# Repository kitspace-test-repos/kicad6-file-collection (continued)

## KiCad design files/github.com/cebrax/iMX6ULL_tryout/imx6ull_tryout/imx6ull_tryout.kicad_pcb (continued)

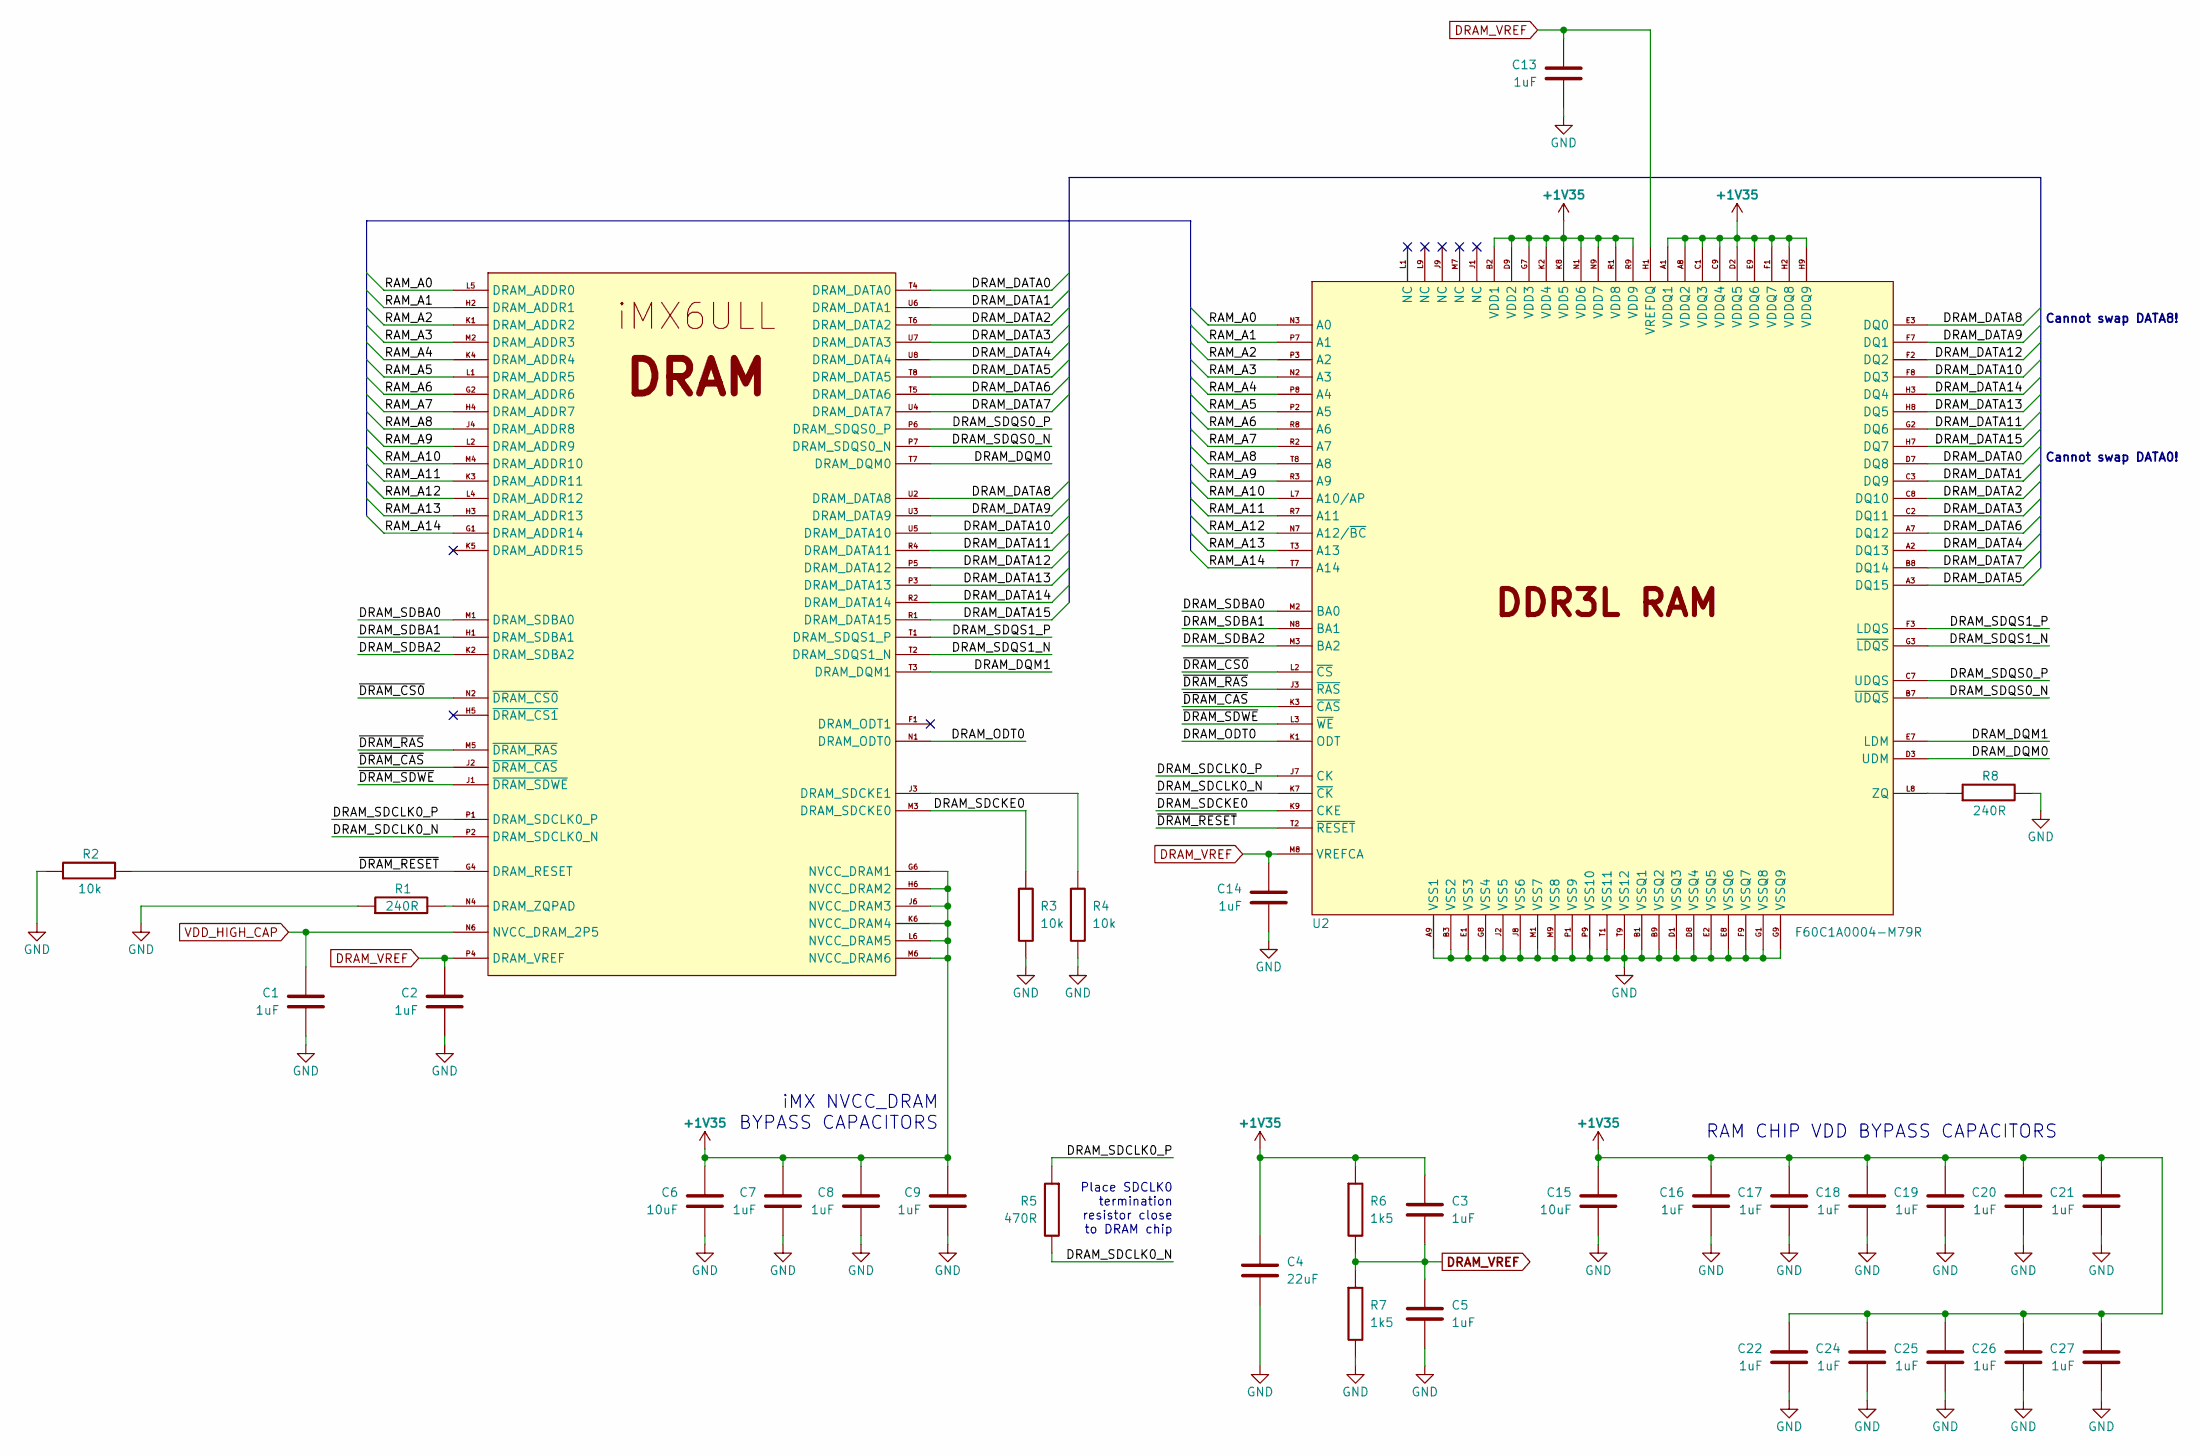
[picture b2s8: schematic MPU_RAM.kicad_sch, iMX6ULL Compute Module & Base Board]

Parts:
C1, C2, C7, C8, C9, C13, C14, C16, C17, C18, C19, C20, C21, C22, C24, C25, C26, C27: 1uF; IPC-SMD-C-0402; Voltage 10V
C3, C5: 1uF; IPC-SMD-C-0603; Voltage 16V
C4: 22uF; IPC-SMD-C-0603; Voltage 6.3V
C6: 10uF; IPC-SMD-C-0402; Voltage 16V
C15: 10uF; IPC-SMD-C-0805; Voltage 16V
R1, R8: 240R; IPC-SMD-R-0402
R2, R3, R4: 10k; IPC-SMD-R-0402
R5: 470R; IPC-SMD-R-0402
R6, R7: 1k5; IPC-SMD-R-0603
U1: iMX6ULL; BGA289C80P17X17_1400X1400X132N
U2: F60C1A0004-M79R; BGA96C80P9X16_1400X800X120

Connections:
+1V35: C3.1, C4.1, C6.1, C7.1, C8.1, C9.1, C15.1, C16.1, C17.1, C18.1, C19.1, C20.1, C21.1, C22.1, C24.1, C25.1, C26.1, C27.1, R6.1, U1.G6 (NVCC_DRAM1), U1.H6 (NVCC_DRAM2), U1.J6 (NVCC_DRAM3), U1.K6 (NVCC_DRAM4), U1.L6 (NVCC_DRAM5), U1.M6 (NVCC_DRAM6), U2.A1 (VDDQ1), U2.A8 (VDDQ2), U2.B2 (VDD1), U2.C1 (VDDQ3), U2.C9 (VDDQ4), U2.D2 (VDDQ5), U2.D9 (VDD2), U2.E9 (VDDQ6), U2.F1 (VDDQ7), U2.G7 (VDD3), U2.H2 (VDDQ8), U2.H9 (VDDQ9), U2.K2 (VDD4), U2.K8 (VDD5), U2.N1 (VDD6), U2.N9 (VDD7), U2.R1 (VDD8), U2.R9 (VDD9); also elsewhere on the board
/MPU_DRAM/DRAM_DATA0: U1.T4 (DRAM_DATA0), U2.D7 (DQ8)
/MPU_DRAM/DRAM_DATA1: U1.U6 (DRAM_DATA1), U2.C3 (DQ9)
/MPU_DRAM/DRAM_DATA2: U1.T6 (DRAM_DATA2), U2.C8 (DQ10)
/MPU_DRAM/DRAM_DATA3: U1.U7 (DRAM_DATA3), U2.C2 (DQ11)
/MPU_DRAM/DRAM_DATA4: U1.U8 (DRAM_DATA4), U2.A2 (DQ13)
/MPU_DRAM/DRAM_DATA5: U1.T8 (DRAM_DATA5), U2.A3 (DQ15)
/MPU_DRAM/DRAM_DATA6: U1.T5 (DRAM_DATA6), U2.A7 (DQ12)
/MPU_DRAM/DRAM_DATA7: U1.U4 (DRAM_DATA7), U2.B8 (DQ14)
/MPU_DRAM/DRAM_DATA8: U1.U2 (DRAM_DATA8), U2.E3 (DQ0)
/MPU_DRAM/DRAM_DATA9: U1.U3 (DRAM_DATA9), U2.F7 (DQ1)
/MPU_DRAM/DRAM_DATA10: U1.U5 (DRAM_DATA10), U2.F8 (DQ3)
/MPU_DRAM/DRAM_DATA11: U1.R4 (DRAM_DATA11), U2.G2 (DQ6)
/MPU_DRAM/DRAM_DATA12: U1.P5 (DRAM_DATA12), U2.F2 (DQ2)
/MPU_DRAM/DRAM_DATA13: U1.P3 (DRAM_DATA13), U2.H8 (DQ5)
/MPU_DRAM/DRAM_DATA14: U1.R2 (DRAM_DATA14), U2.H3 (DQ4)
/MPU_DRAM/DRAM_DATA15: U1.R1 (DRAM_DATA15), U2.H7 (DQ7)
/MPU_DRAM/DRAM_DQM0: U1.T7 (DRAM_DQM0), U2.D3 (UDM)
/MPU_DRAM/DRAM_DQM1: U1.T3 (DRAM_DQM1), U2.E7 (LDM)
/MPU_DRAM/DRAM_ODT0: U1.N1 (DRAM_ODT0), U2.K1 (ODT)
/MPU_DRAM/DRAM_SDBA0: U1.M1 (DRAM_SDBA0), U2.M2 (BA0)
/MPU_DRAM/DRAM_SDBA1: U1.H1 (DRAM_SDBA1), U2.N8 (BA1)
/MPU_DRAM/DRAM_SDBA2: U1.K2 (DRAM_SDBA2), U2.M3 (BA2)
/MPU_DRAM/DRAM_SDCKE0: R3.1, U1.M3 (DRAM_SDCKE0), U2.K9 (CKE)
/MPU_DRAM/DRAM_SDCLK0_N: R5.2, U1.P2 (DRAM_SDCLK0_N), U2.K7 (~CK~)
/MPU_DRAM/DRAM_SDCLK0_P: R5.1, U1.P1 (DRAM_SDCLK0_P), U2.J7 (CK)
/MPU_DRAM/DRAM_SDQS0_N: U1.P7 (DRAM_SDQS0_N), U2.B7 (~UDQS~)
/MPU_DRAM/DRAM_SDQS0_P: U1.P6 (DRAM_SDQS0_P), U2.C7 (UDQS)
/MPU_DRAM/DRAM_SDQS1_N: U1.T2 (DRAM_SDQS1_N), U2.G3 (~LDQS~)
/MPU_DRAM/DRAM_SDQS1_P: U1.T1 (DRAM_SDQS1_P), U2.F3 (LDQS)
/MPU_DRAM/RAM_A0: U1.L5 (DRAM_ADDR0), U2.N3 (A0)
/MPU_DRAM/RAM_A1: U1.H2 (DRAM_ADDR1), U2.P7 (A1)
/MPU_DRAM/RAM_A2: U1.K1 (DRAM_ADDR2), U2.P3 (A2)
/MPU_DRAM/RAM_A3: U1.M2 (DRAM_ADDR3), U2.N2 (A3)
/MPU_DRAM/RAM_A4: U1.K4 (DRAM_ADDR4), U2.P8 (A4)
/MPU_DRAM/RAM_A5: U1.L1 (DRAM_ADDR5), U2.P2 (A5)
/MPU_DRAM/RAM_A6: U1.G2 (DRAM_ADDR6), U2.R8 (A6)
/MPU_DRAM/RAM_A7: U1.H4 (DRAM_ADDR7), U2.R2 (A7)
/MPU_DRAM/RAM_A8: U1.J4 (DRAM_ADDR8), U2.T8 (A8)
/MPU_DRAM/RAM_A9: U1.L2 (DRAM_ADDR9), U2.R3 (A9)
/MPU_DRAM/RAM_A10: U1.M4 (DRAM_ADDR10), U2.L7 (A10/AP)
/MPU_DRAM/RAM_A11: U1.K3 (DRAM_ADDR11), U2.R7 (A11)
/MPU_DRAM/RAM_A12: U1.L4 (DRAM_ADDR12), U2.N7 (A12/~BC~)
/MPU_DRAM/RAM_A13: U1.H3 (DRAM_ADDR13), U2.T3 (A13)
/MPU_DRAM/RAM_A14: U1.G1 (DRAM_ADDR14), U2.T7 (A14)
/MPU_DRAM/~DRAM_CAS: U1.J2 (~DRAM_CAS~), U2.K3 (~CAS~)
/MPU_DRAM/~DRAM_CS0: U1.N2 (~DRAM_CS0~), U2.L2 (~CS~)
/MPU_DRAM/~DRAM_RAS: U1.M5 (~DRAM_RAS~), U2.J3 (~RAS~)
/MPU_DRAM/~DRAM_RESET: R2.2, U1.G4 (DRAM_RESET), U2.T2 (~RESET~)
/MPU_DRAM/~DRAM_SDWE: U1.J1 (~DRAM_SDWE~), U2.L3 (~WE~)
DRAM_VREF: C2.1, C3.2, C5.1, C13.1, C14.1, R6.2, R7.1, U1.P4 (DRAM_VREF), U2.H1 (VREFDQ), U2.M8 (VREFCA)
GND: C1.2, C2.2, C4.2, C5.2, C6.2, C7.2, C8.2, C9.2, C13.2, C14.2, C15.2, C16.2, C17.2, C18.2, C19.2, C20.2, C21.2, C22.2, C24.2, C25.2, C26.2, C27.2, R1.1, R2.1, R3.2, R4.2, R7.2, R8.2, U2.A9 (VSS1), U2.B1 (VSSQ1), U2.B3 (VSS2), U2.B9 (VSSQ2), U2.D1 (VSSQ3), U2.D8 (VSSQ4), U2.E1 (VSS3), U2.E2 (VSSQ5), U2.E8 (VSSQ6), U2.F9 (VSSQ7), U2.G1 (VSSQ8), U2.G8 (VSS4), U2.G9 (VSSQ9), U2.J2 (VSS5), U2.J8 (VSS6), U2.M1 (VSS7), U2.M9 (VSS8), U2.P1 (VSS9), U2.P9 (VSS10), U2.T1 (VSS11), U2.T9 (VSS12); also elsewhere on the board
unnamed: R1.2, U1.N4 (DRAM_ZQPAD)
unnamed: R4.1, U1.J3 (DRAM_SDCKE1)
unnamed: R8.1, U2.L8 (ZQ)
VDD_HIGH_CAP: C1.1, U1.N6 (NVCC_DRAM_2P5); also elsewhere on the board

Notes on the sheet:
iMX NVCC_DRAM BYPASS CAPACITORS
Place SDCLK0 termination resistor close to DRAM chip
RAM CHIP VDD BYPASS CAPACITORS
Cannot swap DATA8!
Cannot swap DATA0!

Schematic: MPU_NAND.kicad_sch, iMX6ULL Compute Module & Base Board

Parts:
C10, C86: 1uF; IPC-SMD-C-0402; Voltage 10V
D3: LED; IPC-SMD-LED-0805
P10: ECSPI4; Connector-Male-Breakaway-7pins
R40, R41, R42, R43, R44: 240R; IPC-SMD-R-0402
R47: 1k5; IPC-SMD-R-0603
U1: iMX6ULL; BGA289C80P17X17_1400X1400X132N

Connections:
ECSPI4_MISO: R43.2, U1.A6 (NAND_DATA6)
ECSPI4_MOSI: R41.2, U1.B6 (NAND_DATA5)
ECSPI4_SCLK: R40.2, U1.C6 (NAND_DATA4)
ECSPI4_SS0: R42.2, U1.A5 (NAND_DATA7)
ECSPI4_SS1: R44.2, U1.B7 (NAND_DATA1)
+3V3: C10.1, C86.1, P10.1, U1.E7 (NVCC_NAND); also elsewhere on the board
GND: C10.2, C86.2, D3.2 (K), P10.7; also elsewhere on the board
unnamed: D3.1 (A), R47.2
unnamed: P10.2, R40.1
unnamed: P10.3, R41.1
unnamed: P10.4, R42.1
unnamed: P10.5, R43.1
unnamed: P10.6, R44.1
unnamed: R47.1, U1.A7 (NAND_DATA2)
SD1_DATA4: U1.A3 (~NAND_READY~)
SD1_DATA5: U1.C5 (~NAND_CE0~)
SD1_DATA6: U1.B5 (~NAND_CE1~)
SD1_DATA7: U1.A4 (NAND_CLE)

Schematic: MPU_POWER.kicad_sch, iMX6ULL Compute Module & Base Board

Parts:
C29, C31, C32, C33, C34, C36, C37, C38, C42, C43, C45: 1uF; IPC-SMD-C-0402; Voltage 10V
C35, C39, C40: 22uF; IPC-SMD-C-0603; Voltage 6.3V
C41, C44, C46: 10uF; IPC-SMD-C-0402; Voltage 16V
U1: iMX6ULL; BGA289C80P17X17_1400X1400X132N

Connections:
+1V35: C29.1, C40.1, U1.H9 (VDD_SOC_IN1), U1.H10 (VDD_SOC_IN2), U1.J9 (VDD_SOC_IN3), U1.J10 (VDD_SOC_IN4), U1.K9 (VDD_SOC_IN5), U1.K10 (VDD_SOC_IN6); also elsewhere on the board
+3V3: C31.1, C32.1, C41.1, U1.L13 (VDDA_ADC_3P3), U1.M13 (ADC_VREFH), U1.N13 (VDD_HIGH_IN), U1.P12 (VDD_SNVS_IN); also elsewhere on the board
/MPU_POWER/NVCC_PLL: C43.1, C44.1, U1.P13 (NVCC_PLL)
/MPU_POWER/VDD_ARM_CAP: C33.1, C34.1, C35.1, U1.G9 (VDD_ARM_CAP_1), U1.G10 (VDD_ARM_CAP_2), U1.G11 (VDD_ARM_CAP_3), U1.H11 (VDD_ARM_CAP_4)
/MPU_POWER/VDD_SNVS_CAP: C42.1, U1.N12 (VDD_SNVS_CAP)
/MPU_POWER/VDD_SOC_CAP: C36.1, C37.1, C38.1, C39.1, U1.G8 (VDD_SOC_CAP1), U1.H8 (VDD_SOC_CAP2), U1.J8 (VDD_SOC_CAP3), U1.J11 (VDD_SOC_CAP4), U1.K8 (VDD_SOC_CAP5), U1.K11 (VDD_SOC_CAP6), U1.L8 (VDD_SOC_CAP7), U1.L9 (VDD_SOC_CAP8), U1.L10 (VDD_SOC_CAP9), U1.L11 (VDD_SOC_CAP10)
GND: C29.2, C31.2, C32.2, C33.2, C34.2, C35.2, C36.2, C37.2, C38.2, C39.2, C40.2, C41.2, C42.2, C43.2, C44.2, C45.2, C46.2, U1.A1 (VSS1), U1.A17 (VSS2), U1.C3 (VSS3), U1.C7 (VSS4), U1.C11 (VSS5), U1.C15 (VSS6), U1.E8 (VSS7), U1.E11 (VSS8), U1.F6 (VSS9), U1.F7 (VSS10), U1.F8 (VSS11), U1.F9 (VSS12), U1.F10 (VSS13), U1.F11 (VSS14), U1.F12 (VSS15), U1.G3 (VSS16), U1.G5 (VSS17), U1.G7 (VSS18), U1.G12 (VSS19), U1.G15 (VSS20), U1.H7 (VSS21), U1.H12 (VSS22), U1.J5 (VSS23), U1.J7 (VSS24), U1.J12 (VSS25), U1.K7 (VSS26), U1.K12 (VSS27), U1.L3 (VSS28), U1.L7 (VSS29), U1.L12 (VSS30), U1.M7 (VSS31), U1.M8 (VSS32), U1.M9 (VSS33), U1.M10 (VSS34), U1.M11 (VSS35), U1.M12 (NGND_KEL0), U1.N3 (VSS36), U1.N5 (VSS37), U1.R3 (VSS38), U1.R5 (VSS39), U1.R7 (VSS40), U1.R11 (VSS41), U1.R16 (VSS42), U1.R17 (VSS43), U1.T14 (VSS44), U1.U1 (VSS45), U1.U14 (VSS46), U1.U17 (VSS47); also elsewhere on the board
VDD_HIGH_CAP: C45.1, C46.1, U1.R14 (VDD_HIGH_CAP1), U1.R15 (VDD_HIGH_CAP2); also elsewhere on the board

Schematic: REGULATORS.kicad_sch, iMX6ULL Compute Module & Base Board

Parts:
C71, C74, C76, C78, C80: 10uF; IPC-SMD-C-0805; Voltage 16V
C72, C77, C81: 220uF; ELKO-DIA-6.5mm-PS-2.54mm; Voltage 16V
C73: 100nF; IPC-SMD-C-0805; Voltage 50V
C75, C79: 100nF; IPC-SMD-C-0805; Voltage V
C82: 1uF; IPC-SMD-C-0402; Voltage 10V
D2: ES1D; IPC-DO-214AC(SMA)
L1, L3: 10uH; Inductor-SMD-FPI0403S-100M
P6: POWER IN; Connector-DG127-5.08-02P
R25, R27, R28: 10k; IPC-SMD-R-0402
R26: 33k2; IPC-SMD-R-0402
R29: 7k68; IPC-SMD-R-0402
U6: 78L05; TO92
U7, U8: TPS56x200; IPC-SOT-23-6

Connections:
+1V35: C80.1, C81.1, L3.1, R29.2; also elsewhere on the board
+3V3: C76.1, C77.1, L1.1, R26.2, R27.1; also elsewhere on the board
+5V: C74.1, U6.1 (VO); also elsewhere on the board
+12V: C71.1, C72.1, C73.1, C78.1, D2.2 (K), P6.1, U6.3 (VI), U7.3 (VIN), U7.5 (EN), U8.3 (VIN)
GND: C71.2, C72.2, C73.2, C74.2, C76.2, C77.2, C78.2, C80.2, C81.2, C82.2, D2.1 (A), P6.2, R25.1, R28.1, U6.2 (GND), U7.1 (GND), U8.1 (GND); also elsewhere on the board
unnamed: C75.1, U7.6 (VBST)
unnamed: C75.2, L1.2, U7.2 (SW)
unnamed: C79.1, U8.6 (VBST)
unnamed: C79.2, L3.2, U8.2 (SW)
unnamed: C82.1, R27.2, U8.5 (EN)
unnamed: R25.2, R26.1, U7.4 (VFB)
unnamed: R28.2, R29.1, U8.4 (VFB)

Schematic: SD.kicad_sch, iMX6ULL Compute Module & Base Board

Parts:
C12, C23, C53, C54, C56, C57, C58: 1uF; IPC-SMD-C-0402; Voltage 10V
C51, C52, C55: 22uF; IPC-SMD-C-0603; Voltage 6.3V
P1: 47352-1001; Connector-uSD-Molex-47352-1001
R14, R15: 10k; IPC-SMD-R-0402
U1: iMX6ULL; BGA289C80P17X17_1400X1400X132N
U3: FEMDRM008G-58A39; 153-VFBGA

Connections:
+3V3: C12.1, C23.1, C51.1, C52.1, C53.1, C54.1, P1.4 (Vdd), R14.1, R15.1, U1.C4 (NVCC_SD1), U3.E6 (VCC), U3.F5 (VCC), U3.J10 (VCC), U3.K9 (VCC); also elsewhere on the board
/SD/eMMC/SD1_CLK: P1.5 (CLK), U1.C1 (SD1_CLK), U3.M6 (CLK)
/SD/eMMC/SD1_CMD: P1.3 (CMD), R15.2, U1.C2 (SD1_CMD), U3.M5 (CMD)
/SD/eMMC/SD1_DATA0: P1.7 (DAT0), R14.2, U1.B3 (SD1_DATA0), U3.A3 (DAT0)
/SD/eMMC/SD1_DATA1: P1.8 (DAT1), U1.B2 (SD1_DATA1), U3.A4 (DAT1)
/SD/eMMC/SD1_DATA2: P1.1 (DAT2), U1.B1 (SD1_DATA2), U3.A5 (DAT2)
/SD/eMMC/SD1_DATA3: P1.2 (DAT3/CD), U1.A2 (SD1_DATA3), U3.B2 (DAT3)
GND: C12.2, C23.2, C51.2, C52.2, C53.2, C54.2, C55.2, C56.2, C57.2, C58.2, P1.6 (Vss), P1.10 (Shield), U3.A6 (VSS), U3.C4 (VSSQ), U3.E7 (VSS), U3.G5 (VSS), U3.H10 (VSS), U3.J5 (VSS), U3.K8 (VSS), U3.N2 (VSSQ), U3.N5 (VSSQ), U3.P4 (VSSQ), U3.P6 (VSSQ); also elsewhere on the board
unnamed: C55.1, C56.1, C57.1, U3.C6 (VCCQ), U3.M4 (VCCQ), U3.N4 (VCCQ), U3.P3 (VCCQ), U3.P5 (VCCQ)
unnamed: C58.1, U3.C2 (VDDI)

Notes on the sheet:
DAT0 and CMD are open drain at the time of initialization
eMMC Option
DNP, No Footprints For future reference only
uSD Option

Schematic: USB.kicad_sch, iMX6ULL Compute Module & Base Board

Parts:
C28, C68: 1uF; IPC-SMD-C-0402; Voltage 10V
C69: 22uF; IPC-SMD-C-0603; Voltage 6.3V
P4, P5: DS1095-WNR0; Connector-USB-A-Female-DS1095-WNR0
U1: iMX6ULL; BGA289C80P17X17_1400X1400X132N

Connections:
+5V: C28.1, P4.1, P5.1, U1.T12 (USB_OTG1_VBUS), U1.U12 (USB_OTG2_VBUS); also elsewhere on the board
/USB/USB1_D_N: P4.2, U1.T15 (USB_OTG1_DN)
/USB/USB1_D_P: P4.3, U1.U15 (USB_OTG1_DP)
/USB/USB2_D_N: P5.2, U1.T13 (USB_OTG2_DN)
/USB/USB2_D_P: P5.3, U1.U13 (USB_OTG2_DP)
GND: C28.2, C68.2, C69.2, P4.5, P5.5; also elsewhere on the board
unnamed: C68.1, C69.1, U1.R12 (VDD_USB_CAP)

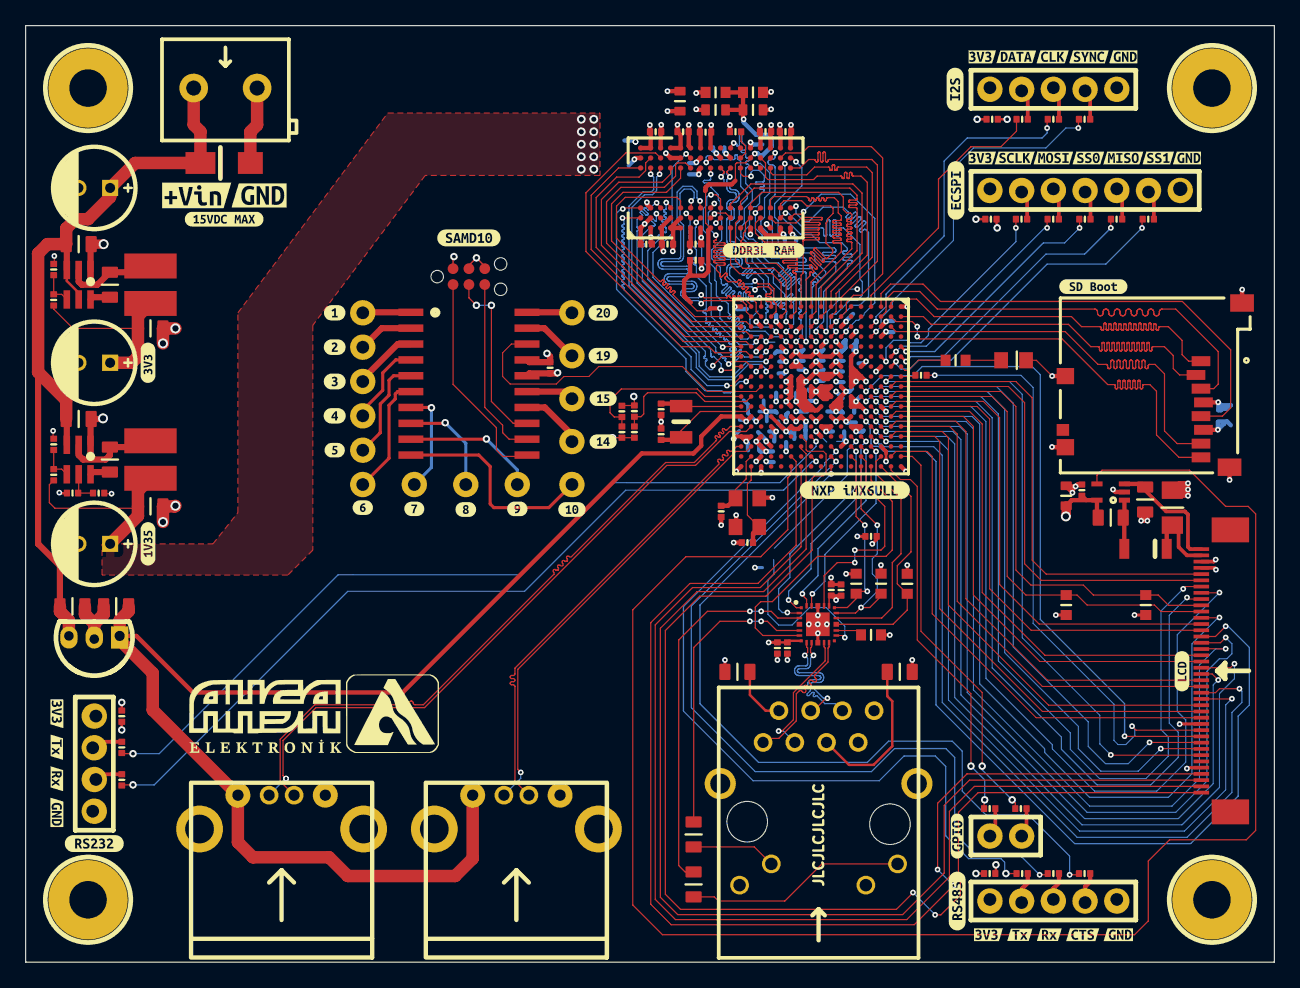
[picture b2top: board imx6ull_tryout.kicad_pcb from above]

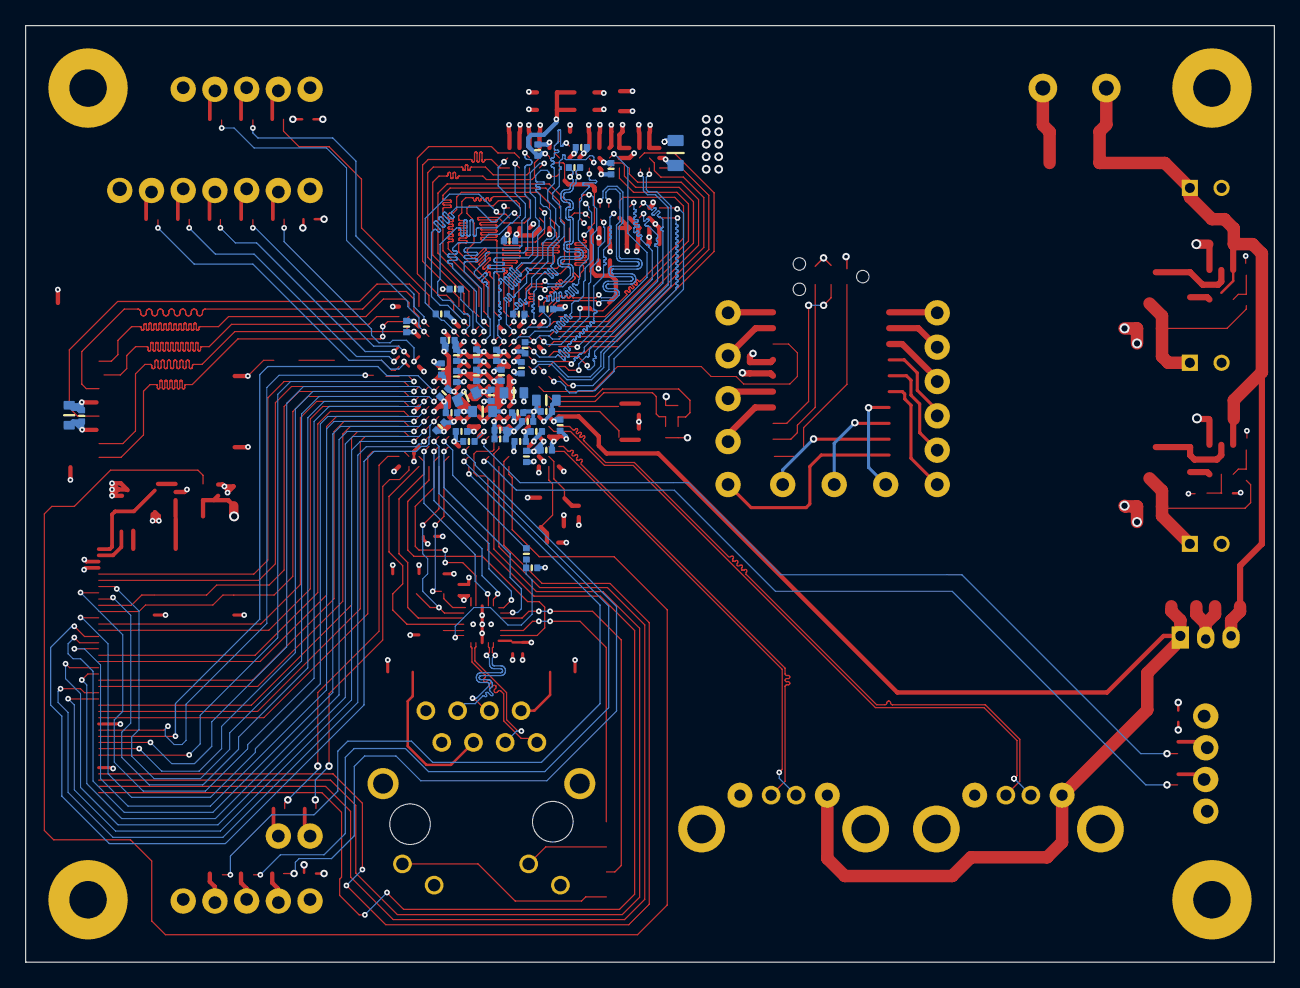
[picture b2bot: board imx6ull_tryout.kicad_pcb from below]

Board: 4 copper layers, 100.0 x 75.0 mm, 222 parts (45 on the bottom side), 199 nets.

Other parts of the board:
C60#2: 1uF; IPC-SMD-C-0402
svg2mod, svg2mod#2, svg2mod#3, svg2mod#4, svg2mod#5, svg2mod#6, svg2mod#7, svg2mod#8, svg2mod#9, svg2mod#10, svg2mod#11, svg2mod#12, svg2mod#13, svg2mod#14, svg2mod#15, svg2mod#16, svg2mod#17, svg2mod#18, svg2mod#19, svg2mod#20, svg2mod#21, svg2mod#22, svg2mod#23, svg2mod#24, svg2mod#25, svg2mod#26, svg2mod#27, svg2mod#28, svg2mod#29, svg2mod#30, svg2mod#31, svg2mod#32, svg2mod#33, svg2mod#34, svg2mod#35, svg2mod#36, svg2mod#37, svg2mod#38, svg2mod#39, svg2mod#40, svg2mod#41, svg2mod#42, svg2mod#43, svg2mod#44, svg2mod#45, svg2mod#46, svg2mod#47, svg2mod#48, svg2mod#49, svg2mod#50: G***; svg2mod

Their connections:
+3V3: C60#2.1; also elsewhere on the board
GND: C60#2.2; also elsewhere on the board

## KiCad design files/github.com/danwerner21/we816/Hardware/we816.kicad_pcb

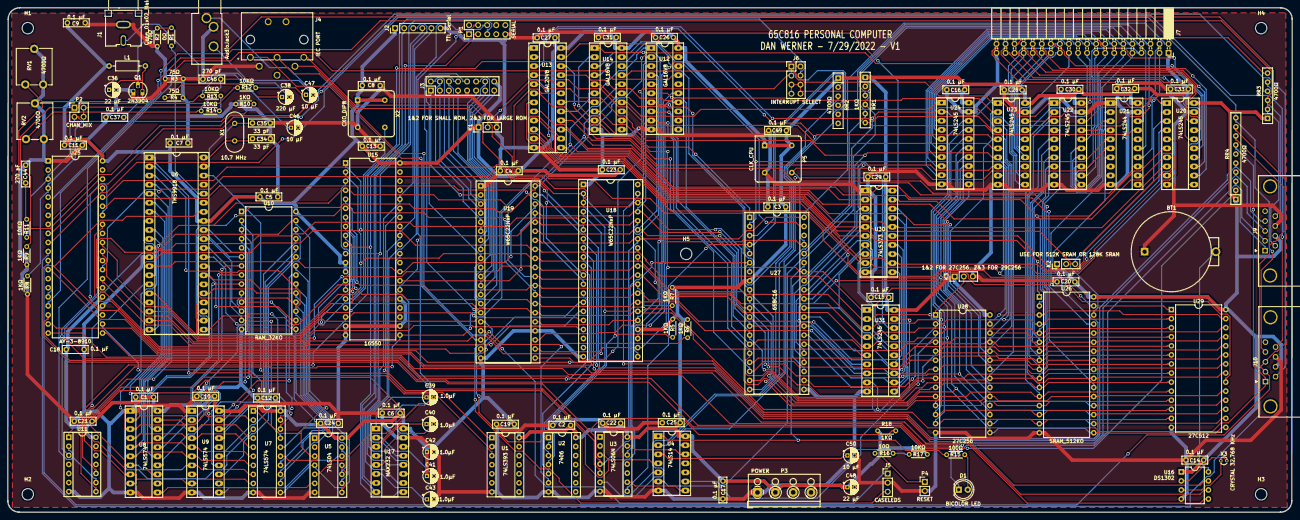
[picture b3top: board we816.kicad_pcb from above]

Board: 2 copper layers, 360.1 x 141.4 mm, 135 parts (0 on the bottom side), 248 nets.

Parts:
BT1: Battery_Cell; Battery_Holder_Coin_2032_BS-7_FIXED
C1, C2, C3, C4, C5, C6, C7, C8, C9, C10, C11, C12, C13, C14, C15, C16, C17, C18, C19, C20, C21, C22, C23, C24, C25, C26, C27, C28, C29, C30, C31, C32, C33, C37, C49: 0.1 µF; C_Rect_L7.0mm_W2.0mm_P5.00mm
C34, C35: 33 pF; C_Rect_L7.0mm_W2.0mm_P5.00mm
C36, C48: 22 µF; CP_Radial_D4.0mm_P2.00mm
C38: 220 µF; CP_Radial_D4.0mm_P2.00mm
C39, C40, C41, C42, C43: 1.0µF; CP_Radial_D4.0mm_P2.00mm
C44, C45: 270 pF; C_Rect_L7.0mm_W2.0mm_P5.00mm
C46, C47, C50: 10 µF; CP_Radial_D4.0mm_P2.00mm
D1: BICOLOR LED; LED_D5.0mm
H1, H2, H3, H4, H5: MountingHole; MountingHole_3.2mm_M3
J1: Conn_01x02_Male; CUI_RCJ-041
J2: TTL Serial; PinHeader_1x06_P2.54mm_Vertical
J3: KEYBOARD; PinHeader_2x08_P2.54mm_Vertical
J4: IEC PORT; din6
J5: CASELEDS; PinHeader_1x03_P2.54mm_Vertical
J6: INTERRUPT SELECT; PinHeader_2x04_P2.54mm_Vertical
J7: expansion port; PinSocket_2x20_P2.54mm_Horizontal
J8: AudioJack3; Jack_3.5mm_CUI_SJ1-3533NG_Horizontal_CircularHoles
J9, J10: DB9_Male; DSUB-9_Male_Horizontal_P2.77x2.84mm_EdgePinOffset9.90mm_Hou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
K1: 1&2 FOR SMALL ROM, 2&3 FOR LARGE ROM; PinHeader_1x03_P2.54mm_Vertical
K2: USE FOR 512K SRAM OR 128K SRAM; PinHeader_1x03_P2.54mm_Vertical
K3: 1&2 FOR 27C256, 2&3 FOR 29C256; PinHeader_1x03_P2.54mm_Vertical
L1: INDUCTOR (BEAD); R_Axial_DIN0207_L6.3mm_D2.5mm_P10.16mm_Horizontal
P1: SERIAL; PinHeader_2x05_P2.54mm_Vertical
P2: CHAN_MIX; PinHeader_2x02_P2.54mm_Vertical
P3: POWER; TerminalBlock_RND_205-00003_1x04_P5.00mm_Horizontal
P4: RESET; PinHeader_1x02_P2.54mm_Vertical
P5: CLK_CPU; Oscillator_DIP-8
Q1: 2N3904; TO-92L_HandSolder
R1: 0Ω; R_Axial_DIN0204_L3.6mm_D1.6mm_P5.08mm_Horizontal
R2: 470Ω; R_Axial_DIN0204_L3.6mm_D1.6mm_P5.08mm_Horizontal
R3, R4: 75Ω; R_Axial_DIN0204_L3.6mm_D1.6mm_P5.08mm_Horizontal
R5, R6, R7, R8, R9, R10, R18: 1KΩ; R_Axial_DIN0204_L3.6mm_D1.6mm_P5.08mm_Horizontal
R11, R12, R13, R14, R17: 10KΩ; R_Axial_DIN0204_L3.6mm_D1.6mm_P5.08mm_Horizontal
R15: 100Ω; R_Axial_DIN0204_L3.6mm_D1.6mm_P5.08mm_Horizontal
R16: 10Ω; R_Axial_DIN0204_L3.6mm_D1.6mm_P5.08mm_Horizontal
RR1: 1KΩ; R_Array_SIP6
RR2, RR3: 4700Ω; R_Array_SIP6
RR4: 4700Ω; R_Array_SIP10
RV1, RV2: 4700Ω; Potentiometer_ACP_CA9-V10_Vertical
U1: 74LS393; DIP-14_W7.62mm_Socket
U2: 7406; DIP-14_W7.62mm_Socket
U3: 74LS06N; DIP-14_W7.62mm_Socket
U4: 74LS14; DIP-14_W7.62mm_Socket_LongPads
U5: 74LS04; DIP-14_W7.62mm_Socket
U6: TMS9918; DIP-40_W15.24mm_Socket_LongPads
U7: 74LS574; DIP-20_W7.62mm_Socket
U8, U9: 74LS574; DIP-20_W7.62mm_Socket_LongPads
U10: RAM_32KO; DIP-28_W15.24mm
U11: 74LS32; DIP-14_W7.62mm_Socket
U12, U14: GAL16V8; DIP-20_W7.62mm_Socket_LongPads
U13: GAL20V8; DIP-24_W7.62mm_Socket_LongPads
U15: 16550; DIP-40_W15.24mm
U16: DS1302; DIP-8_W7.62mm
U17: MAX232; DIP-16_W7.62mm_Socket_LongPads
U18, U19: W65C22NxP; DIP-40_W15.24mm_Socket
U20, U22, U23, U24, U31: 74LS245; DIP-20_W7.62mm_Socket_LongPads
U21: 74LS244; DIP-20_W7.62mm_Socket_LongPads
U25: AY-3-8910; DIP-40_W15.24mm
U26: SRAM_512KO; DIP-32_W15.24mm
U27: 658C16; DIP-40_W15.24mm_Socket
U28: 27C256; DIP-28_W15.24mm
U29: 27C512; DIP-28_W15.24mm
U30: 74LS373; DIP-20_W7.62mm_Socket_LongPads
X1: 10.7 MHz; Crystal_HC18-U_Vertical
X2: CXO_DIP8; Oscillator_DIP-8
X3: CRYSTAL 32.768 KHz; Crystal_Round_D1.5mm_Vertical

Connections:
/Video/COMVID: C38.2, J1.2
A0: U6.13 (MODE), U12.2 (I2), U15.28 (A0), U18.38 (RS0), U19.38 (RS0), U22.2 (A0), U26.12 (A0), U27.9 (A0), U28.10 (A0), U29.10 (A0)
A1: U12.3 (I3), U15.27 (A1), U18.37 (RS1), U19.37 (RS1), U22.3 (A1), U26.11 (A1), U27.10 (A1), U28.9 (A1), U29.9 (A1)
A2: U12.4 (I4), U15.26 (A2), U18.36 (RS2), U19.36 (RS2), U22.4 (A2), U26.10 (A2), U27.11 (A2), U28.8 (A2), U29.8 (A2)
A3: U12.5 (I5), U18.35 (RS3), U19.35 (RS3), U22.5 (A3), U26.9 (A3), U27.12 (A3), U28.7 (A3), U29.7 (A3)
A4: U12.6 (I6), U22.6 (A4), U26.8 (A4), U27.13 (A4), U28.6 (A4), U29.6 (A4)
A5: U12.7 (I7), U22.7 (A5), U26.7 (A5), U27.14 (A5), U28.5 (A5), U29.5 (A5)
A6: U12.8 (I8), U22.8 (A6), U26.6 (A6), U27.15 (A6), U28.4 (A6), U29.4 (A6)
A7: U12.9 (I9), U22.9 (A7), U26.5 (A7), U27.16 (A7), U28.3 (A7), U29.3 (A7)
A8: U13.21 (IO21), U23.2 (A0), U26.27 (A8), U27.17 (A8), U28.25 (A8), U29.25 (A8)
A9: U13.22 (IO22), U23.3 (A1), U26.26 (A9), U27.18 (A9), U28.24 (A9), U29.24 (A9)
A10: U13.2 (I2), U23.4 (A2), U26.23 (A10), U27.19 (A10), U28.21 (A10), U29.21 (A10)
A11: U13.3 (I3), U23.5 (A3), U26.25 (A11), U27.20 (A11), U28.23 (A11), U29.23 (A11)
A12: U13.4 (I4), U23.6 (A4), U26.4 (A12), U27.22 (A12), U28.2 (A12), U29.2 (A12)
A13: U13.5 (I5), U23.7 (A5), U26.28 (A13), U27.23 (A13), U28.26 (A13), U29.26 (A13)
A14: U13.6 (I6), U23.8 (A6), U26.3 (A14), U27.24 (A14), U28.27 (A14), U29.27 (A14)
A15: U13.7 (I7), U23.9 (A7), U26.31 (A15), U27.25 (A15), U29.1 (A15)
A16: U13.8 (I8), U20.2 (A0), U26.2 (A16), U30.2 (O0)
A17: K2.3, U13.9 (I9), U20.3 (A1), U30.5 (O1)
A18: U13.10 (I10), U20.4 (A2), U26.1 (A18), U30.6 (O2)
A19: U13.11 (I11), U20.5 (A3), U30.9 (O3)
A20: U13.14 (I14), U20.6 (A4), U30.12 (O4)
A21: U13.1 (I1), U20.7 (A5), U30.15 (O5)
A22: U13.13 (I13), U20.8 (A6), U30.16 (O6)
A23: U13.23 (I23), U20.9 (A7), U30.19 (O7)
ABORT: RR2.4 (R3), U27.3 (~ABORT)
AD0: U27.33 (AD0), U30.3 (D0), U31.18 (B0)
AD1: U27.32 (AD1), U30.4 (D1), U31.17 (B1)
AD2: U27.31 (AD2), U30.7 (D2), U31.16 (B2)
AD3: U27.30 (AD3), U30.8 (D3), U31.15 (B3)
AD4: U27.29 (AD4), U30.13 (D4), U31.14 (B4)
AD5: U27.28 (AD5), U30.14 (D5), U31.13 (B5)
AD6: U27.27 (AD6), U30.17 (D6), U31.12 (B6)
AD7: U27.26 (AD7), U30.18 (D7), U31.11 (B7)
BUS: U13.18 (IO18), U14.7 (I7)
BUSAK: U14.17 (I03), U20.1 (A->B), U22.1 (A->B), U23.1 (A->B)
BUSRQ: U21.3 (O3b), U27.36 (BE)
B_A0: J7.3, U22.18 (B0)
B_A1: J7.5, U22.17 (B1)
B_A2: J7.7, U22.16 (B2)
B_A3: J7.9, U22.15 (B3)
B_A4: J7.11, U22.14 (B4)
B_A5: J7.13, U22.13 (B5)
B_A6: J7.15, U22.12 (B6)
B_A7: J7.17, U22.11 (B7)
B_A8: J7.19, U23.18 (B0)
B_A9: J7.21, U23.17 (B1)
B_A10: J7.23, U23.16 (B2)
B_A11: J7.25, U23.15 (B3)
B_A12: J7.27, U23.14 (B4)
B_A13: J7.29, U23.13 (B5)
B_A14: J7.31, U23.12 (B6)
B_A15: J7.33, U23.11 (B7)
B_A16: J7.35, U20.18 (B0)
B_A17: J7.37, U20.17 (B1)
B_A18: J7.38, U20.16 (B2)
B_A19: J7.36, U20.15 (B3)
B_A20: J7.34, U20.14 (B4)
B_A21: J7.32, U20.13 (B5)
B_A22: J7.30, U20.12 (B6)
B_A23: J7.28, U20.11 (B7)
B_BUSRQ: RR1.6 (R5), U21.17 (I3b)
B_CLK_CPU: J7.4, U21.14 (O2a)
B_D0: J7.26, U24.2 (A0)
B_D1: J7.24, U24.3 (A1)
B_D2: J7.22, U24.4 (A2)
B_D3: J7.20, U24.5 (A3)
B_D4: J7.18, U24.6 (A4)
B_D5: J7.16, U24.7 (A5)
B_D6: J7.14, U24.8 (A6)
B_D7: J7.12, U24.9 (A7)
B_INT: J6.5, J6.6, J6.7, J6.8, J7.10, RR1.4 (R3), U4.9
B_NMI: J7.6, RR1.5 (R4), U4.13
B_RW: J7.40, U21.18 (O0a)
B_WAIT: J7.8, RR1.3 (R2), U21.15 (I2b)
CLK_AUDIO: U1.1 (CP), U6.38 (CPUCLK)
CLK_CPU: P5.5 (OUT), U4.5, U14.1 (I1/CLK), U18.25 (CLK), U19.25 (CLK), U21.6 (I2a), U27.37 (CLK)
CLK_UART: U15.16 (XIN), X2.5 (OUT)
COLUMN0: J3.1, U19.2 (PA0)
COLUMN1: J3.2, U19.3 (PA1)
COLUMN2: J3.3, U19.4 (PA2)
COLUMN3: J3.4, U19.5 (PA3)
COLUMN4: J3.5, U19.6 (PA4)
COLUMN5: J3.6, U19.7 (PA5)
COLUMN6: J3.7, U19.8 (PA6)
COLUMN7: J3.8, U19.9 (PA7)
COMP_VID: R1.2, U6.36 (COMVID)
CS_RAM: U13.16 (IO16), U26.22 (CE#)
CS_ROM: U13.15 (IO15), U28.20 (~CE)
CS_UART: U12.19 (IO1), U15.14 (~CS2)
CS_VDP: U11.2, U11.9, U12.17 (I03)
CS_VIA1: U12.15 (IO5), U18.23 (~CS2)
CS_VIA2: U12.14 (IO6), U19.23 (~CS2)
CTS: P1.6, U17.13 (R1IN)
CTS_TTL: J2.3, U15.36 (~CTS), U17.12 (R1OUT)
D0: U6.17 (D7), U15.1 (D0), U18.33 (D0), U19.33 (D0), U24.18 (B0), U26.13 (DQ0), U28.11 (D0), U29.11 (D0), U31.2 (A0)
D1: U6.18 (D6), U15.2 (D1), U18.32 (D1), U19.32 (D1), U24.17 (B1), U26.14 (DQ1), U28.12 (D1), U29.12 (D1), U31.3 (A1)
D2: U6.19 (D5), U15.3 (D2), U18.31 (D2), U19.31 (D2), U24.16 (B2), U26.15 (DQ2), U28.13 (D2), U29.13 (D2), U31.4 (A2)
D3: U6.20 (D4), U15.4 (D3), U18.30 (D3), U19.30 (D3), U24.15 (B3), U26.17 (DQ3), U28.15 (D3), U29.15 (D3), U31.5 (A3)
D4: U6.21 (D3), U15.5 (D4), U18.29 (D4), U19.29 (D4), U24.14 (B4), U26.18 (DQ4), U28.16 (D4), U29.16 (D4), U31.6 (A4)
D5: U6.22 (D2), U15.6 (D5), U18.28 (D5), U19.28 (D5), U24.13 (B5), U26.19 (DQ5), U28.17 (D5), U29.17 (D5), U31.7 (A5)
D6: U6.23 (D1), U15.7 (D6), U18.27 (D6), U19.27 (D6), U24.12 (B6), U26.20 (DQ6), U28.18 (D6), U29.18 (D6), U31.8 (A6)
D7: U6.24 (D0), U15.8 (D7), U18.26 (D7), U19.26 (D7), U24.11 (B7), U26.21 (DQ7), U28.19 (D7), U29.19 (D7), U31.9 (A7)
DATA_DIR: U14.14 (IO6), U24.1 (A->B)
EMU: R15.2, U4.1, U27.35 (E)
GND: BT1.2 (-), C1.2, C2.2, C3.2, C4.2, C5.2, C6.2, C7.2, C8.2, C9.2, C10.2, C11.2, C12.2, C13.2, C14.2, C15.2, C16.2, C17.2, C18.2, C19.2, C20.2, C21.2, C22.2, C23.2, C24.2, C25.2, C26.2, C27.2, C28.2, C29.2, C30.2, C31.2, C32.2, C33.2, C34.2, C35.2, C36.2, C37.2, C42.2, C43.2, C44.1, C45.2, C48.2, C49.2, C50.2, J1.1, J2.6, J3.9, J4.2, J5.2, J7.39, J8.T, J9.8, J10.8, K1.3, K3.3, P1.9, P3.1, P4.2, P5.4 (GND), Q1.1 (E), R2.2, R3.1, R3.2, R4.1, R8.2, R9.2, R10.2, RV1.1, RV1.2, RV2.1, RV2.2, U1.2 (MR), U1.7 (GND), U2.7 (GND), U3.7 (GND), U4.7 (GND), U5.7 (GND), U6.12 (VSS), U7.10 (GND), U8.1 (OE), U8.10 (GND), U9.1 (OE), U9.10 (GND), U10.14 (GND), U11.7 (GND), U12.10 (GND), U13.12 (GND), U14.10 (GND), U15.19 (WR), U15.20 (GND), U15.22 (RD), U15.25 (~ADS), U16.4 (GND), U17.15 (GND), U18.1 (VSS), U19.1 (VSS), U20.10 (GND), U20.19 (CE), U21.1 (OEa), U21.10 (GND), U21.19 (OEb), U22.10 (GND), U22.19 (CE), U23.10 (GND), U23.19 (CE), U24.10 (GND), U24.19 (CE), U25.1 (VSS), U25.24 (~A9), U26.16 (VSS), U27.21 (GND), U28.14 (GND), U29.14 (GND), U30.1 (OE), U30.10 (GND), U31.10 (GND), X2.4 (GND)
INT: RR2.2 (R1), U3.8, U27.4 (~INT)
IO: U12.1 (I1/CLK), U13.17 (IO17), U14.6 (I6)
KB_CAPS_LED: J3.11, U19.14 (PB4)
KB_GRAPH_LED: J3.10, U19.15 (PB5)
LED_1: J5.3, U19.16 (PB6)
LED_2: J5.1, U19.17 (PB7)
LED_ANODE: D1.1 (K), U21.7 (O1b)
ML: U14.5 (I5), U27.5 (~ML)
NMI: RR2.3 (R2), U3.12, U27.6 (~NMI)
N_EMU: U4.2, U21.13 (I1b)
unnamed: BT1.1 (+), U16.8 (VCC1)
unnamed: C34.1, U6.40 (X1), X1.1
unnamed: C35.1, U6.39 (X2), X1.2
unnamed: C36.1, C37.1, L1.2, Q1.3 (C)
unnamed: C38.1, R4.2
unnamed: C39.1, U17.1 (C1+)
unnamed: C39.2, U17.3 (C1-)
unnamed: C40.1, U17.4 (C2+)
unnamed: C40.2, U17.5 (C2-)
unnamed: C41.2, U17.2 (VS+)
unnamed: C43.1, U17.6 (VS-)
unnamed: C44.2, C46.1, R11.1, R13.2, RV1.3
unnamed: C45.1, C47.1, R12.1, R14.2, RV2.3
unnamed: C46.2, J8.S
unnamed: C47.2, J8.R
unnamed: C50.1, R16.1, R17.2, U4.3
unnamed: D1.2 (A), R15.1
unnamed: J4.3, R6.2, U2.6
unnamed: J6.1, U3.6
unnamed: K1.2, U13.20 (I020)
unnamed: K2.2, U26.30 (A17)
unnamed: K3.2, U28.1 (VPP)
unnamed: P2.1, R9.1, R12.2, U25.38 (C)
unnamed: P2.2, P2.4, R8.1, R13.1, R14.1, U25.4 (B)
unnamed: P2.3, R10.1, R11.2, U25.3 (A)
unnamed: P4.1, R16.2
unnamed: Q1.2 (B), R1.1, R2.1
unnamed: U1.3 (Q0), U25.22 (CLOCK)
unnamed: U3.9, U4.8
unnamed: U3.13, U4.12
unnamed: U5.10, U5.13
unnamed: U5.8, U5.11
unnamed: U9.14 (Q5), U10.2 (A12)
unnamed: U9.19 (Q0), U10.3 (A7)
unnamed: U8.13 (Q6), U10.4 (A6)
unnamed: U8.14 (Q5), U10.5 (A5)
unnamed: U8.15 (Q4), U10.6 (A4)
unnamed: U8.16 (Q3), U10.7 (A3)
unnamed: U8.17 (Q2), U10.8 (A2)
unnamed: U8.18 (Q1), U10.9 (A1)
unnamed: U8.19 (Q0), U10.10 (A0)
unnamed: U9.16 (Q3), U10.21 (A10)
unnamed: U9.15 (Q4), U10.23 (A11)
unnamed: U9.17 (Q2), U10.24 (A9)
unnamed: U9.18 (Q1), U10.25 (A8)
unnamed: U9.13 (Q6), U10.26 (A13)
unnamed: U15.9 (RCLK), U15.15 (~BAUDOUT)
unnamed: U16.2 (X1), X3.2
unnamed: U16.3 (X2), X3.1
unnamed: U4.6, U30.11 (LE), U31.19 (CE)
O1_ROM: U13.19 (IO19), U29.20 (~CE)
P1_A: J9.6, RR3.2 (R1), U25.17 (IOA4)
P1_B: J9.9, RR3.3 (R2), U25.16 (IOA5)
P1_D: J9.2, RR4.3 (R2), U25.20 (IOA1)
P1_L: J9.3, RR4.4 (R3), U25.19 (IOA2)
P1_R: J9.4, RR4.5 (R4), U25.18 (IOA3)
P1_U: J9.1, RR4.2 (R1), U25.21 (IOA0)
P2_A: J10.6, RR3.4 (R3), U25.9 (IOB4)
P2_B: J10.9, RR3.5 (R4), U25.8 (IOB5)
P2_D: J10.2, RR4.8 (R7), U25.12 (IOB1)
P2_L: J10.3, RR4.9 (R8), U25.11 (IOB2)
P2_R: J10.4, RR4.10 (R9), U25.10 (IOB3)
P2_U: J10.1, RR4.7 (R6), U25.13 (IOB0)
RD: U11.10, U14.16 (IO4), U15.21 (~RD), U26.24 (OE#), U28.22 (~OE), U29.22 (~OE)
RESET: J7.2, R18.2, U3.4, U6.34 (~RESET), U18.34 (~RESET), U19.34 (~RESET), U25.23 (~RESET), U27.40 (~RESET)
ROWA: J3.15, U19.10 (PB0)
ROWB: J3.14, U19.11 (PB1)
ROWC: J3.13, U19.12 (PB2)
ROWD: J3.12, U19.13 (PB3)
RTS: P1.4, U17.14 (T1OUT)
RTS_TTL: J2.5, U15.32 (~RTS), U17.11 (T1IN)
RW: U14.2 (I2), U18.22 (R/~W), U19.22 (R/~W), U21.2 (I0a), U27.34 (R~W), U31.1 (A->B)
RX: P1.3, U17.8 (R2IN)
SERATNOUT: U2.5, U18.9 (PA7)
SERCLKIN: J4.4, R5.2, U2.4, U18.2 (PA0)
SERCLKOUT: U2.3, U19.39 (CA2)
SERDATAIN: J4.5, R7.2, U2.2, U18.3 (PA1)
SERDATAOUT: U2.1, U19.19 (CB2)
SERSRQ: J4.1, U19.18 (CB1)
SIN_TTL: J2.2, U15.10 (SIN), U17.9 (R2OUT)
SOUT_TTL: J2.4, U15.11 (SOUT), U17.10 (T2IN)
TX: P1.5, U17.7 (T2OUT)
UART_INT: U3.5, U15.30 (INTR)
URESET: U3.3, U4.4, U15.35 (MR)
USERA_2: U18.4 (PA2), U25.27 (BDIR)
USERA_3: U18.5 (PA3), U25.29 (BC1)
USERA_4: U18.6 (PA4), U25.28 (BC2)
USERA_5: U16.6 (I/O), U18.7 (PA5)
USERA_6: U16.5 (CE), U18.8 (PA6)
USERB_0: U18.10 (PB0), U25.37 (DA0)
USERB_1: U18.11 (PB1), U25.36 (DA1)
USERB_2: U18.12 (PB2), U25.35 (DA2)
USERB_3: U18.13 (PB3), U25.34 (DA3)
USERB_4: U18.14 (PB4), U25.33 (DA4)
USERB_5: U18.15 (PB5), U25.32 (DA5)
USERB_6: U18.16 (PB6), U25.31 (DA6)
USERB_7: U18.17 (PB7), U25.30 (DA7)
USERCA_2: U16.7 (SCLK), U18.39 (CA2)
VAD0: U6.10 (AD0), U7.2 (D0)
VAD1: U6.9 (AD1), U7.3 (D1), U8.2 (D0), U9.2 (D0)
VAD2: U6.8 (AD2), U7.4 (D2), U8.3 (D1), U9.3 (D1)
VAD3: U6.7 (AD3), U7.5 (D3), U8.4 (D2), U9.4 (D2)
VAD4: U6.6 (AD4), U7.6 (D4), U8.5 (D3), U9.5 (D3)
VAD5: U6.5 (AD5), U7.7 (D5), U8.6 (D4), U9.6 (D4)
VAD6: U6.4 (AD6), U7.8 (D6), U8.7 (D5), U9.7 (D5)
VAD7: U6.3 (AD7), U7.9 (D7), U8.8 (D6), U8.9 (D7), U9.8 (D6), U9.9 (D7)
VCAS: U5.9, U6.2 (CAS), U10.20 (~CS)
VCC: C1.1, C2.1, C3.1, C4.1, C5.1, C6.1, C7.1, C8.1, C9.1, C10.1, C11.1, C12.1, C13.1, C14.1, C15.1, C16.1, C17.1, C18.1, C19.1, C20.1, C21.1, C22.1, C23.1, C24.1, C25.1, C26.1, C27.1, C28.1, C29.1, C30.1, C31.1, C32.1, C33.1, C41.1, C42.1, C48.1, C49.1, J2.1, J3.16, J7.1, J9.7, J10.7, K1.1, K2.1, K3.1, L1.1, P3.2, P5.1 (EN), P5.8 (Vcc), R5.1, R6.1, R7.1, R17.1, R18.1, RR1.1 (common), RR2.1 (common), RR3.1 (common), RR4.1 (common), U1.14 (VCC), U2.14 (VCC), U3.14 (VCC), U4.14 (VCC), U5.14 (VCC), U6.33 (VCC), U7.20 (VCC), U8.20 (VCC), U9.20 (VCC), U10.28 (VCC), U11.14 (VCC), U12.20 (VCC), U13.24 (VCC), U14.20 (VCC), U15.12 (CS0), U15.13 (CS1), U15.40 (VCC), U16.1 (VCC2), U17.16 (VCC), U18.20 (VCC), U18.24 (CS1), U19.20 (VCC), U19.24 (CS1), U20.20 (VCC), U21.20 (VCC), U22.20 (VCC), U23.20 (VCC), U24.20 (VCC), U25.25 (A8), U25.40 (VCC), U26.32 (VCC), U27.8 (VCC), U28.28 (VCC), U29.28 (VCC), U30.20 (VCC), U31.20 (VCC), X2.1 (EN), X2.8 (Vcc)
VCOL: U5.12, U9.11 (Cp)
VD0: U6.32 (RD0), U7.19 (Q0), U10.11 (Q0)
VD1: U6.31 (RD1), U7.18 (Q1), U10.12 (Q1)
VD2: U6.30 (RD2), U7.17 (Q2), U10.13 (Q2)
VD3: U6.29 (RD3), U7.16 (Q3), U10.15 (Q3)
VD4: U6.28 (RD4), U7.15 (Q4), U10.16 (Q4)
VD5: U6.27 (RD5), U7.14 (Q5), U10.17 (Q5)
VD6: U6.26 (RD6), U7.13 (Q6), U10.18 (Q6)
VD7: U6.25 (RD7), U7.12 (Q7), U10.19 (Q7)
VDA: U14.3 (I3), U27.39 (VDA)
VDPRD: U6.15 (CSR), U11.8
VDPWR: U6.14 (CSW), U11.3
VIA1_INT: J6.2, U18.21 (~IRQ)
VIA2_INT: J6.3, U19.21 (~IRQ)
VP: U14.8 (I8), U27.1 (~VP)
VPA: U14.4 (I4), U27.7 (VPA)
VRAM_BANK: RR3.6 (R5), U10.1 (A14), U19.40 (CA1)
VRAS: U5.5, U6.1 (RAS)
VRD: U5.4, U7.11 (Cp), U10.22 (~OE)
VROW: U5.6, U8.11 (Cp)
VRW: U5.3, U6.11 (R/~W), U7.1 (OE), U10.27 (~WE)
V_INT: J6.4, U6.16 (~IRQ)
WAIT: U21.5 (O2b), U27.2 (RDY)
WR: U11.1, U14.15 (IO5), U15.18 (~WR), U26.29 (WE#)
